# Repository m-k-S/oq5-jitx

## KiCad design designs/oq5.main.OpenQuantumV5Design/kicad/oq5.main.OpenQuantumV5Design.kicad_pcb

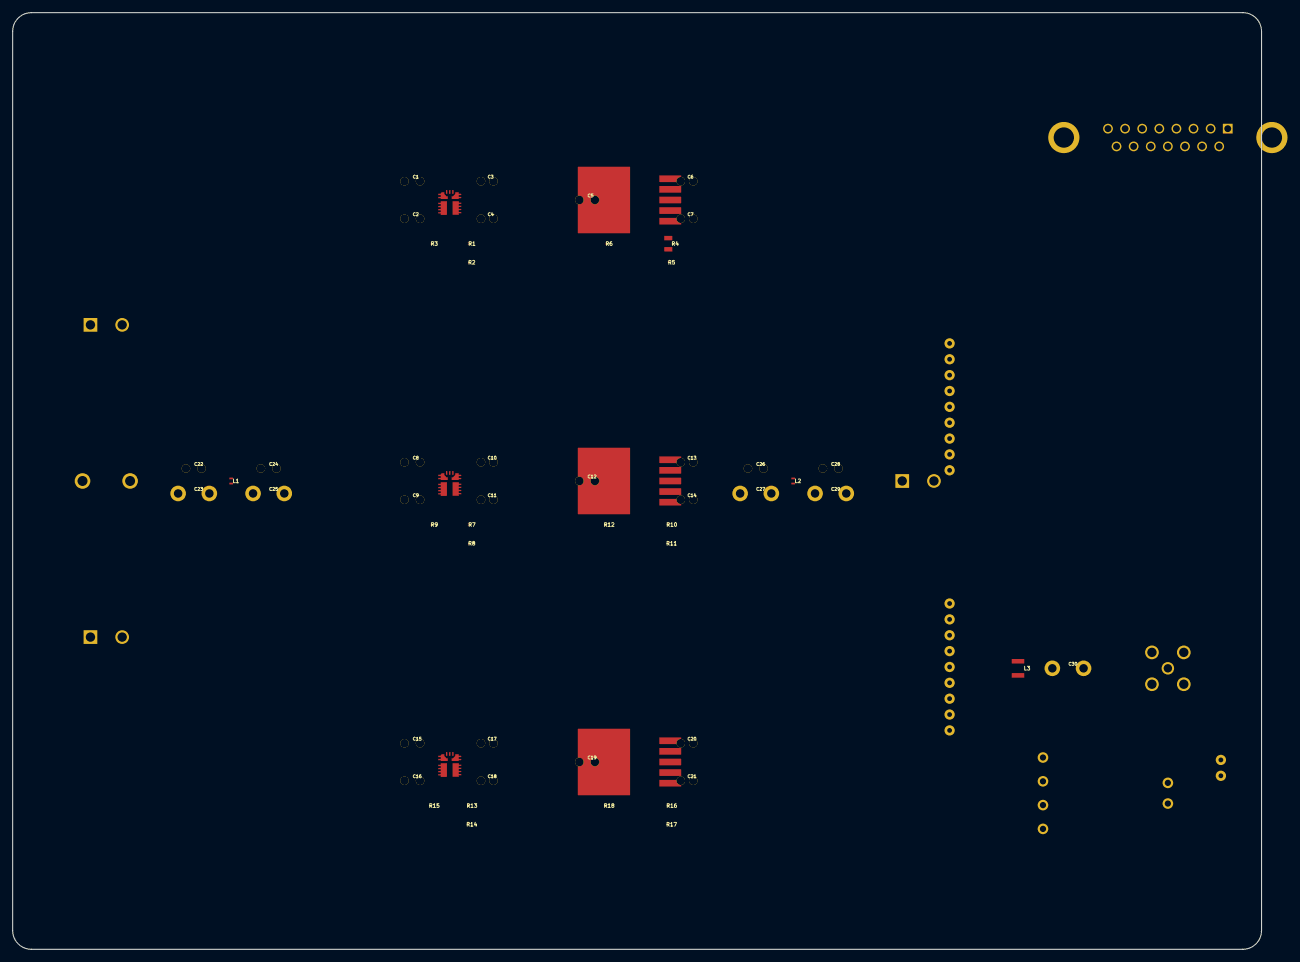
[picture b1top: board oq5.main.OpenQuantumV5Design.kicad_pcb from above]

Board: 2 copper layers, 200.0 x 150.0 mm, 66 parts (0 on the bottom side), 32 nets, no tracks yet.

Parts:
C1: 10 µF; LANDPATTERN__15
C2: 10 µF; LANDPATTERN__16
C3: 22 µF; LANDPATTERN__17
C4: 22 µF; LANDPATTERN__18
C5: 10 µF; LANDPATTERN__19
C6: 22 µF; LANDPATTERN__20
C7: 22 µF; LANDPATTERN__21
C8: 10 µF; LANDPATTERN__22
C9: 10 µF; LANDPATTERN__23
C10: 22 µF; LANDPATTERN__24
C11: 22 µF; LANDPATTERN__25
C12: 10 µF; LANDPATTERN__26
C13: 22 µF; LANDPATTERN__27
C14: 22 µF; LANDPATTERN__28
C15: 10 µF; LANDPATTERN__29
C16: 10 µF; LANDPATTERN_
C17: 22 µF; LANDPATTERN__1
C18: 22 µF; LANDPATTERN__2
C19: 10 µF; LANDPATTERN__3
C20: 22 µF; LANDPATTERN__4
C21: 22 µF; LANDPATTERN__5
C22: 10 µF; LANDPATTERN__6
C23: 100 nF; LANDPATTERN__7
C24: 10 µF; LANDPATTERN__8
C25: 100 nF; LANDPATTERN__9
C26: 10 µF; LANDPATTERN__10
C27: 100 nF; LANDPATTERN__11
C28: 10 µF; LANDPATTERN__12
C29: 100 nF; LANDPATTERN__13
C30: 100 nF; LANDPATTERN__14
J1: CTL200; KOHERONLANDPATTERN
J2: 1717729; PHOENIXCONTACT1717729LP
J3, J4, J5: 1729128; PHOENIXCONTACT1729128LP
J6: XM3B-1522-502; DB15LANDPATTERN
J7: RFENABLELANDPATTERN
J8: VTUNELANDPATTERN
L1: 10 µH; LANDPATTERN0402
L2: 10 µH; LANDPATTERN0402_1
L3: 470 µH; LANDPATTERN1007
R1: 133 kΩ; LANDPATTERN01005_2
R2: 10.005 kΩ; LANDPATTERN009005_4
R3: 10.005 kΩ; LANDPATTERN009005_5
R4: 46 kΩ; LANDPATTERN0805
R5: 10.005 kΩ; LANDPATTERN009005_6
R6: 10.005 kΩ; LANDPATTERN009005_7
R7: 107 kΩ; LANDPATTERN01005_3
R8: 10.005 kΩ; LANDPATTERN009005_8
R9: 10.005 kΩ; LANDPATTERN009005_9
R10: 30 kΩ; LANDPATTERN01005_4
R11: 10.005 kΩ; LANDPATTERN009005_10
R12: 10.005 kΩ; LANDPATTERN009005_11
R13: 107 kΩ; LANDPATTERN01005
R14: 10.005 kΩ; LANDPATTERN009005
R15: 10.005 kΩ; LANDPATTERN009005_1
R16: 30 kΩ; LANDPATTERN01005_1
R17: 10.005 kΩ; LANDPATTERN009005_2
R18: 10.005 kΩ; LANDPATTERN009005_3
RF1: BWSMA-KE-Z001; SMALANDPATTERN
U1, U3, U5: TPSM863252RDXR; TPSM863252LANDPATTERN
U2, U4, U6: NCP5663DSADJR4G; NCP5663LANDPATTERN

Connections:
Adj: R16.2, R17.1, U6.p5
EN: R3.2, U1.p6
Enable: R12.2, U4.p1
FB: R7.2, R8.1, U3.p7
PGND: C1.2, C2.2, C3.2, C4.2, C5.2, C6.2, C7.2, C8.2, C9.2, C10.2, C11.2, C12.2, C13.2, C14.2, C15.2, C16.2, C17.2, C18.2, C19.2, C20.2, C21.2, C22.2, C23.2, C24.2, C25.2, C26.2, C27.2, C28.2, C29.2, J1.gnd1, J1.gnd2, J1.gnd3, J1.gnd4, J1.gnd5, J1.gnd6, J1.gnd7, J2.p2, J3.p2, J4.p2, J5.p2, J6.MH1, J6.MH2, J7.p2, J8.p4, R2.2, R5.2, R8.2, R11.2, R14.2, R17.2, RF1.gnd1, RF1.gnd2, RF1.gnd3, RF1.gnd4, U1.p4, U2.p3, U2.p6, U3.p4, U4.p3, U4.p6, U5.p4, U6.p3, U6.p6
VIN: C1.1, C2.1, C8.1, C9.1, C15.1, C16.1, C24.1, C25.1, J3.p1, J4.p1, L1.2, R3.1, R9.1, R15.1, U1.p1, U3.p1, U5.p1
VOUT: C17.1, C18.1, C19.1, R13.1, R18.1, U5.p3, U6.p2
Vout: C6.1, C7.1, J1.vs, R4.1, U2.p4
buck_7v_package_VOUT: C3.1, C4.1, C5.1, R1.1, R6.1, U1.p3, U2.p2
buck_redpitaya_package_EN: R9.2, U3.p6
buck_vco_package_FB: R13.2, R14.1, U5.p7
l_p1: J8.p3, L3.1
l_p2: C28.1, C29.1, J5.p1, L2.2
ld_n: J1.ld_n, J6.p9
ld_p: J1.ld_p, J6.p1
ldo_7v_package_Adj: R4.2, R5.1, U2.p5
ldo_redpitaya_package_Vout: C13.1, C14.1, C26.1, C27.1, L2.1, R10.1, U4.p4
ldo_vco_package_Enable: R18.2, U6.p1
p1: C22.1, C23.1, J2.p1, L1.1
p2: C30.2, J6.p8, L3.2
p15: J6.p15, J7.p1
package_Adj: R10.2, R11.1, U4.p5
package_EN: R15.2, U5.p6
package_Enable: R6.2, U2.p1
package_FB: R1.2, R2.1, U1.p7
package_VOUT: C10.1, C11.1, C12.1, R7.1, R12.1, U3.p3, U4.p2
package_Vout: C20.1, C21.1, J6.p7, R16.1, U6.p4
sig: C30.1, RF1.sig
tec_n1: J1.tec_n1, J1.tec_n2, J6.p2
tec_p1: J1.tec_p1, J1.tec_p2, J6.p3
th_n: J1.th_n, J6.p5
th_p: J1.th_p, J6.p4

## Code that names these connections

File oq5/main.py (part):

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
class DB15Landpattern(Landpattern):
    # Row 1 (pins 1-8)
    LD_P = _THRect(1.57, 1.57, 1.1).at(9.59, 1.42)     # Pin 1
    PELT_N = _THCircle(1.57, 1.1).at(6.85, 1.42)        # Pin 2
    PELT_P = _THCircle(1.57, 1.1).at(4.11, 1.42)        # Pin 3
    TH_P = _THCircle(1.57, 1.1).at(1.37, 1.42)          # Pin 4
    TH_N = _THCircle(1.57, 1.1).at(-1.37, 1.42)         # Pin 5
    NC6 = _THCircle(1.57, 1.1).at(-4.11, 1.42)          # Pin 6
    VCO_5V = _THCircle(1.57, 1.1).at(-6.85, 1.42)       # Pin 7
    VTUNE_MOD = _THCircle(1.57, 1.1).at(-9.59, 1.42)    # Pin 8
    # Row 2 (pins 9-15)
    LD_N = _THCircle(1.57, 1.1).at(8.22, -1.42)         # Pin 9
    NC10 = _THCircle(1.57, 1.1).at(5.48, -1.42)         # Pin 10
    NC11 = _THCircle(1.57, 1.1).at(2.74, -1.42)         # Pin 11
    NC12 = _THCircle(1.57, 1.1).at(0.0, -1.42)          # Pin 12
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    mpn = "XM3B-1522-502"
    manufacturer = "Omron Electronics"
    reference_designator_prefix = "J"
    LD_P = Port()       # Pin 1
    PELT_N = Port()     # Pin 2
    PELT_P = Port()     # Pin 3
    TH_P = Port()       # Pin 4
    TH_N = Port()       # Pin 5
    NC6 = Port()        # Pin 6
    VCO_5V = Port()     # Pin 7
    VTUNE_MOD = Port()  # Pin 8
    LD_N = Port()       # Pin 9
    NC10 = Port()       # Pin 10
    NC11 = Port()       # Pin 11
    NC12 = Port()       # Pin 12
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
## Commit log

2026-03-30 some basic placement
2026-03-31 fixing netlist
